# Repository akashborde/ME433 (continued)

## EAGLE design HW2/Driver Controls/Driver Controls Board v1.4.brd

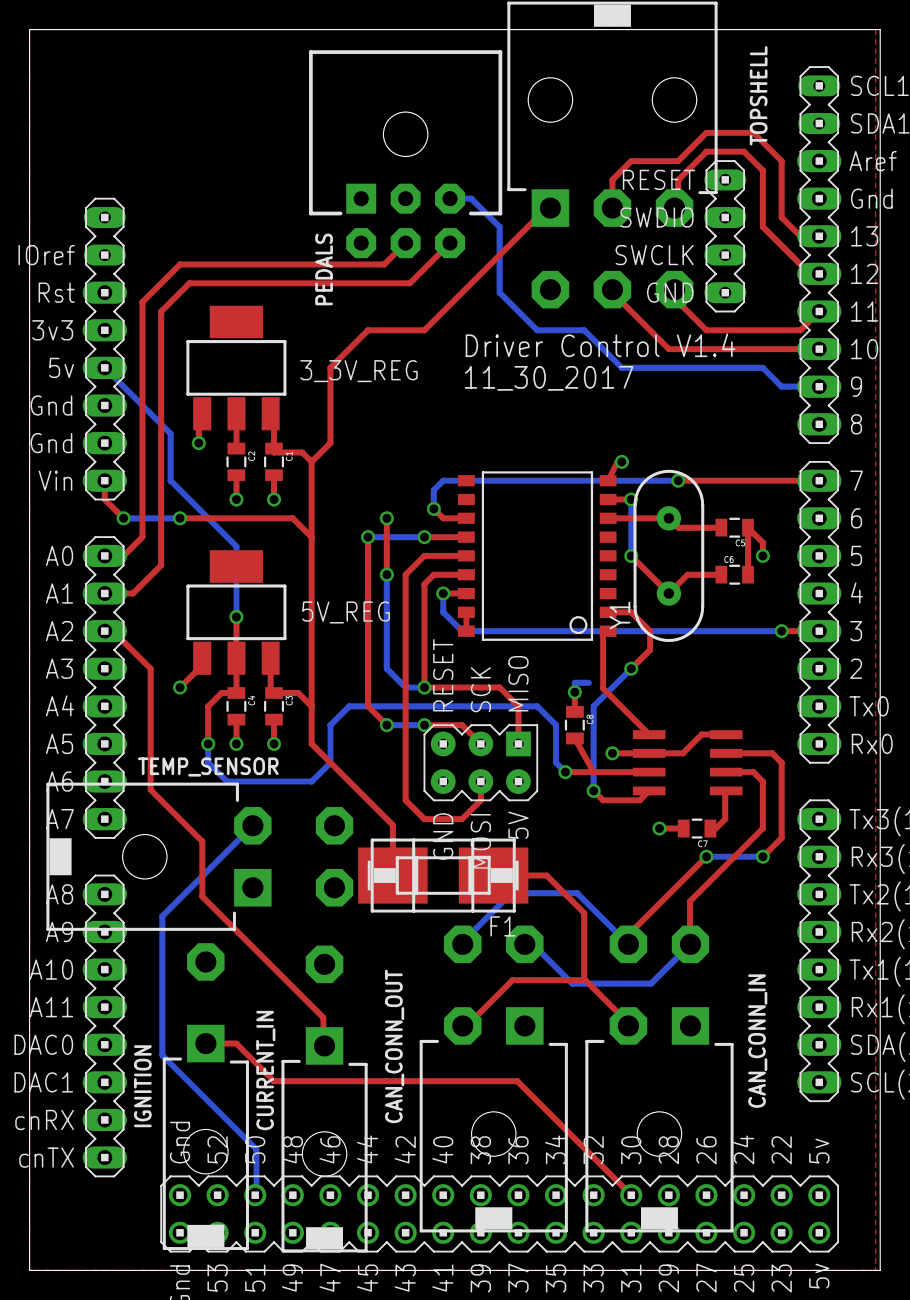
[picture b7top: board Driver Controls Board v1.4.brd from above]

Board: 2 copper layers, 57.5 x 83.8 mm, 22 parts (0 on the bottom side), 26 nets.

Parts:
3_3V_REG: NCP1117ST33T3G; SOT223
5V_REG: NCP1117ST50T3G; SOT223
C1, C2, C3, C4: 10µF; 0805
C5, C6: 0805
C7, C8: .1µF; 0805
CAN_CONN_IN: 39-30-04?; 39-30-?04?
CAN_CONN_OUT: 39-30-04?; 39-30-?04?
CURRENT_IN: 39-30-02?_S; 39-30-?02?
F1: SMD-MICRO-FUSE-BLOCK; OMNIBLOK
IGNITION: 39-30-02?_S; 39-30-?02?
PEDALS: 43045-06_S; 43045-06
TEMP_SENSOR: 39-30-04?; 39-30-?04?
TOPSHELL: 39-30-06?_S; 39-30-?06?
U$2: DUE(NORMAL)
U$6: MCP2562; SOIC8
U$7: MCP2515; SO-18W
Y1: HC49US

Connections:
3.3V: 3_3V_REG.2, C2.1, C7.1, PEDALS.1, TEMP_SENSOR.1, U$2.3V3, U$6.5, U$7.17, U$7.18
5V: 5V_REG.2, C4.1, C8.2, U$2.5V, U$6.3
12V: 3_3V_REG.3, 5V_REG.3, C1.1, C3.1, F1.P$2, TOPSHELL.1, U$2.VIN
ACCEL: PEDALS.5, U$2.A0
BRAKE: TOPSHELL.2, U$2.13
BRAKE_PED: PEDALS.3, U$2.9
CAN+: CAN_CONN_IN.2, CAN_CONN_OUT.2, F1.P$1
CAN_CS: U$2.3, U$7.16
CAN_H: CAN_CONN_IN.4, CAN_CONN_OUT.4, U$6.7
CAN_INT: U$2.7, U$7.12
CAN_L: CAN_CONN_IN.3, CAN_CONN_OUT.3, U$6.6
CAN_RX: U$6.4, U$7.2
CAN_TX: U$6.1, U$7.1
CUR_IN: CURRENT_IN.1, U$2.A2
GND: 3_3V_REG.1, 5V_REG.1, C1.2, C2.2, C3.2, C4.2, C5.1, C6.2, C7.2, C8.1, CAN_CONN_IN.1, CAN_CONN_OUT.1, CURRENT_IN.2, IGNITION.2, PEDALS.4, TEMP_SENSOR.3, TOPSHELL.4, U$2.GND_1, U$2.GND_2, U$6.2, U$6.8, U$7.9
HEADLIGHTS: TOPSHELL.5, U$2.10
IGNITION: IGNITION.1, U$2.30
L_TURN: TOPSHELL.3, U$2.12
MISO: U$2.MISO_ICSP, U$7.15
MOSI: U$2.MOSI_ICSP, U$7.14
unnamed: C5.2, U$7.7, Y1.2
unnamed: C6.1, U$7.8, Y1.1
REGEN: PEDALS.6, U$2.A1
R_TURN: TOPSHELL.6, U$2.11
SCK: U$2.SCK_ICSP, U$7.13
SENSOR_IN: TEMP_SENSOR.2, U$2.50

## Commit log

2019-04-02 deleted a .zip file from shared repo
2019-04-02 circuit diagram
2019-04-02 power supply without capacitors
2019-04-03 power supply with capacitors
2019-04-03 full breadboard pic
2019-04-03 new project initialization with pragmas
2019-04-03 pragma settings configured
2019-04-03 turn LED off when button is pushed
2019-04-03 almost done, just need to implement 1kHz blinking logic
2019-04-04 HW1 final code, with 1kHz scope and LED off with pushbutton
2019-04-08 PIC32 symbol created
2019-04-13 progress on the pcb
2019-04-13 most of schematic
2019-04-16 removed submodule of HW4
2019-04-16 re-adding HW4 to github
2019-04-16 some spi starter code
2019-04-17 as much of spi initialization as i can do right now
2019-04-17 working spi channel
2019-04-17 setVoltage works correctly!
2019-04-19 working SPI with proper output voltage waveforms
2019-04-22 Library and Schematic for PIC32 breakout board
2019-04-24 working i2c code
2019-04-24 reuploading images
2019-04-24 adding ckt diagram
2019-04-24 more robust i2c demonstration code and video
2019-04-24 5Hz heartbeat and pushbutton added for i2c
2019-04-25 successful read from WHOAMI
2019-04-26 HW6 working code, except for frame rate counter
2019-04-26 Frame rate counter added
2019-04-30 accelerometer + progress bars activated
2019-04-30 video of accelerometer in x-y direction and progress bars
2019-05-01 hw7 recreated with harmony
2019-05-07 successful usb + imu reading upon key press
2019-05-08 working touchscreen and touchscreen game
2019-05-14 copied hw10 content into hw11 folder, since hw11 is based on hw10
2019-05-15 working imu as a mouse with video
2019-05-20 added image of plots
2019-05-23 CAD images of wheel and box
2019-05-23 cleaning up git error
2019-05-30 HW15
2019-06-11 TechCup Code: Robot drives in a line or a predefined circle
2019-06-12 TechCup HW16 Final Submission
